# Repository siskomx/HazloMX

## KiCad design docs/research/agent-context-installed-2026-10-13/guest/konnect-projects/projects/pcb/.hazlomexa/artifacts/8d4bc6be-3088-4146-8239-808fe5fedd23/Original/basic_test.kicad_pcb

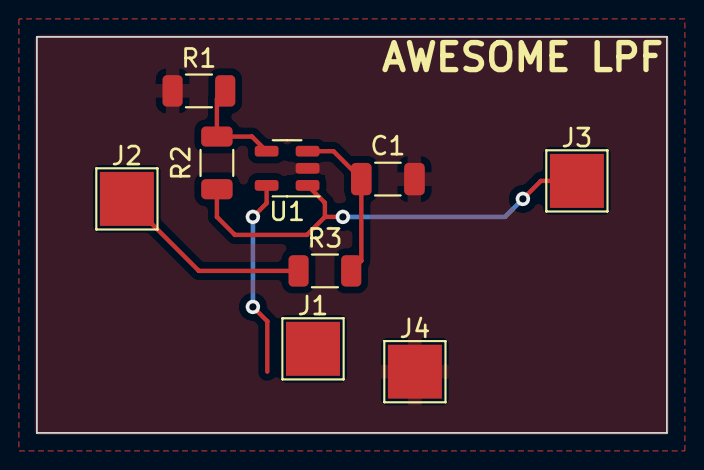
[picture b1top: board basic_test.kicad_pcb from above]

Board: 2 copper layers, 35.0 x 22.0 mm, 9 parts (0 on the bottom side), 6 nets.

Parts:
C1: 10u; C_1206_3216Metric
J1, J2, J3, J4: Conn_01x01_Pin; TestPoint_Pad_3.0x3.0mm
R1, R2, R3: 10k; R_1206_3216Metric
U1: TLV2371DBV; SOT-23-5

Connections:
/IN: J2.1, R3.1
/OUT: J3.1, R2.2, U1.1
/VCC: J1.1, U1.5 (V+)
GND: C1.2, J4.1, R1.1, U1.2 (V-)
unnamed: C1.1, R3.2, U1.3 (+)
unnamed: R1.2, R2.1, U1.4 (-)
